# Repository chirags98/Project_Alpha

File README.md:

# Project_Alpha

Changes made:
1) Supply to R8 was changed from -10V to +10V.
2) Track width was increased from 10 mil to 24 mil.
3) Bypass capacitor was added for 8051.
4) GND planewas shifted to bottom layer and given isolation setting of 16 mil.

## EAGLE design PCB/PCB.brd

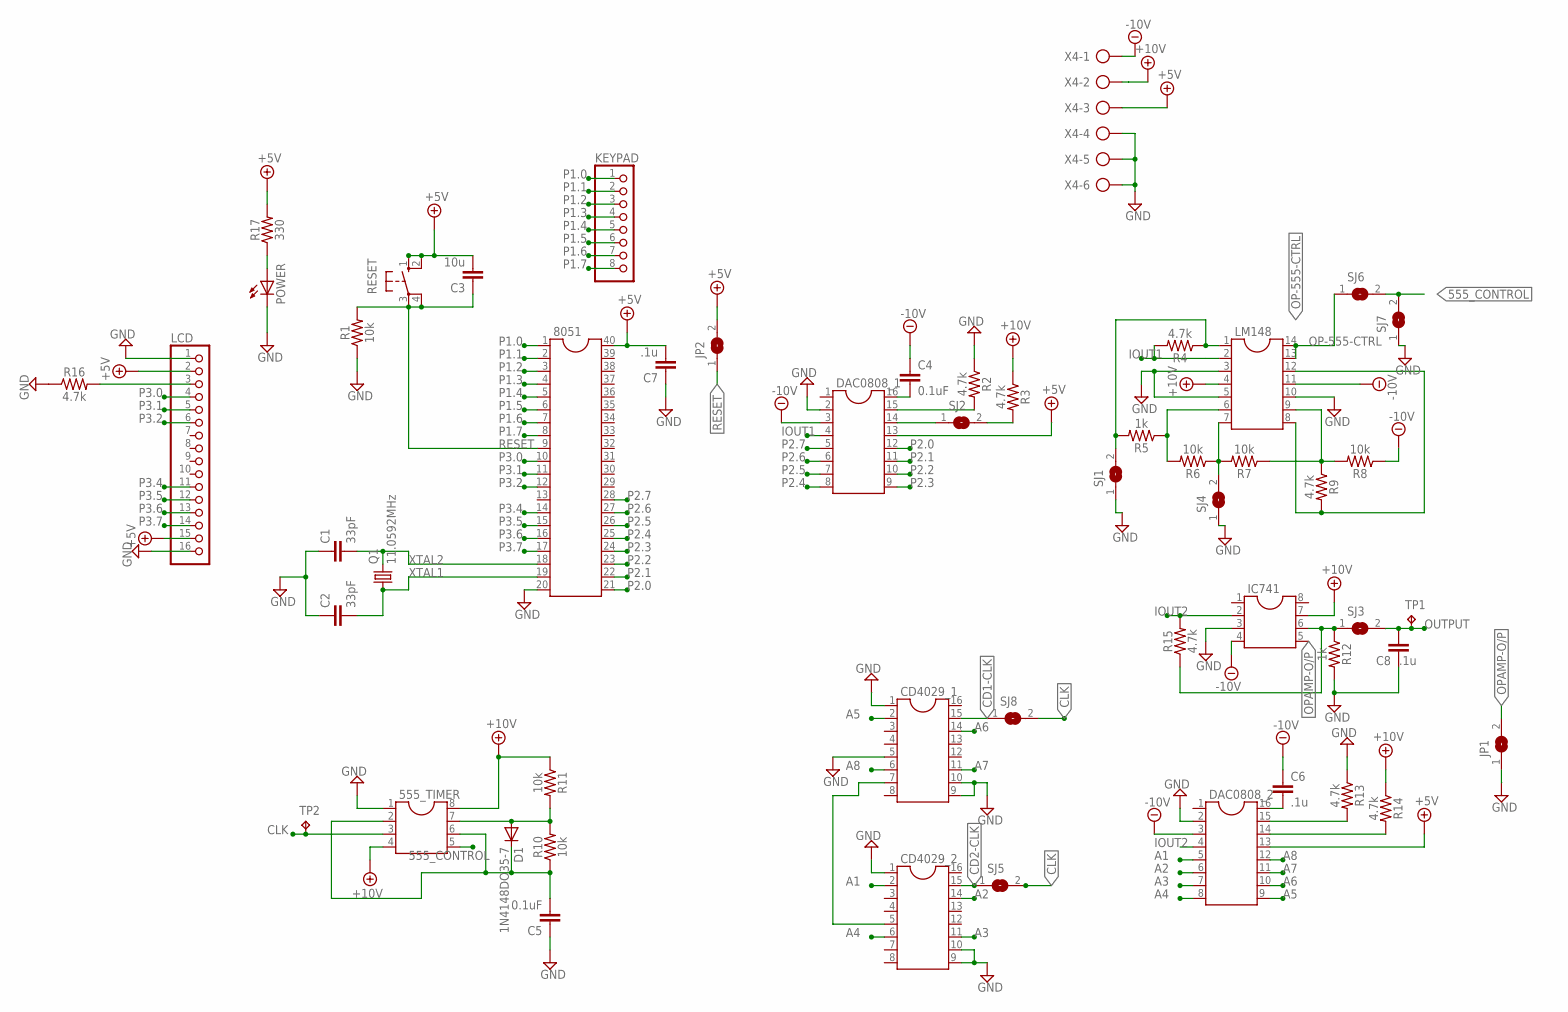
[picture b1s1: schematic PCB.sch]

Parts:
555_TIMER: DIL8; DIL08
8051: DIL40; MPN PIC-USB-4550
C1, C2: 33pF; C025-025X050
C3: 10u; C025-025X050
C4, C5: 0.1uF; C025-025X050
C6, C7, C8: .1u; C025-025X050
CD4029_1, CD4029_2: DIL16
D1: 1N4148DO35-7; DO35-7
DAC0808_1, DAC0808_2: DIL16
IC741: DIL8; DIL08
JP1, JP2: SJ
KEYPAD: PINHD-1X8; 1X08
LCD: PINHD-1X16; 1X16
LM148: DIL14
POWER: LED5MM
Q1: 11.0592MHz; HC49/S; MPN HC49SM-3.6864-30-50-60-16-ATF
R1, R6, R7, R8, R10, R11: 10k; AXIAL-0.3
R2, R3, R4, R9, R13, R14, R15, R16: 4.7k; AXIAL-0.3
R5, R12: 1k; AXIAL-0.3
R17: 330; AXIAL-0.3
RESET: 10-XX; B3F-10XX
SJ1, SJ2, SJ3, SJ4, SJ5, SJ6, SJ7, SJ8: SJ
TP1, TP2: TPPAD1-20; P1-20
X4: AK500/6-H

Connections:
555_CONTROL: 555_TIMER.5, SJ6.2, SJ7.2
+5V: 8051.40, C3.2, C7.2, DAC0808_1.13, DAC0808_2.13, JP2.2, LCD.2, LCD.15, R17.P$2 (2), RESET.1 (S), RESET.2 (S1), X4.3
+10V: 555_TIMER.4, 555_TIMER.8, IC741.7, LM148.4, R3.P$1 (1), R11.P$1 (1), R14.P$1 (1), X4.2
-10V: C4.1, C6.1, DAC0808_1.3, DAC0808_2.3, IC741.4, LM148.11, R8.P$1 (1), X4.1
A1: CD4029_2.2, DAC0808_2.5
A2: CD4029_2.14, DAC0808_2.6
A3: CD4029_2.11, DAC0808_2.7
A4: CD4029_2.6, DAC0808_2.8
A5: CD4029_1.2, DAC0808_2.9
A6: CD4029_1.14, DAC0808_2.10
A7: CD4029_1.11, DAC0808_2.11
A8: CD4029_1.6, DAC0808_2.12
CD1-CLK: CD4029_1.15, SJ8.1
CD2-CLK: CD4029_2.15, SJ5.1
CLK: 555_TIMER.3, SJ5.2, SJ8.2, TP2.TP
GND: 555_TIMER.1, 8051.20, C1.1, C2.1, C5.1, C7.1, C8.1, CD4029_1.1, CD4029_1.5, CD4029_1.9, CD4029_1.10, CD4029_2.1, CD4029_2.9, CD4029_2.10, DAC0808_1.2, DAC0808_2.2, IC741.3, JP1.1, LCD.1, LCD.16, LM148.3, LM148.5, LM148.10, POWER.K (C), R1.P$1 (1), R2.P$1 (1), R12.P$2 (2), R13.P$1 (1), R16.P$1 (1), SJ1.1, SJ4.1, SJ7.1, X4.4, X4.5, X4.6
IOUT1: DAC0808_1.4, LM148.2, R4.P$2 (2)
IOUT2: DAC0808_2.4, IC741.2, R15.P$2 (2)
unnamed: DAC0808_1.15, R2.P$2 (2)
unnamed: R3.P$2 (2), SJ2.2
unnamed: C4.2, DAC0808_1.16
unnamed: LM148.7, R6.P$1 (1), R7.P$2 (2), SJ4.2
unnamed: LM148.1, R4.P$1 (1), R5.P$2 (2), SJ1.2
unnamed: LM148.6, R5.P$1 (1), R6.P$2 (2)
unnamed: LM148.9, R7.P$1 (1), R8.P$2 (2), R9.P$1 (1)
unnamed: 555_TIMER.7, D1.A, R10.P$2 (2), R11.P$2 (2)
unnamed: 555_TIMER.2, 555_TIMER.6, C5.2, D1.C, R10.P$1 (1)
unnamed: DAC0808_2.15, R13.P$2 (2)
unnamed: DAC0808_2.14, R14.P$2 (2)
unnamed: C6.2, DAC0808_2.16
unnamed: CD4029_1.7, CD4029_2.5
unnamed: POWER.A, R17.P$1 (1)
unnamed: DAC0808_1.14, SJ2.1
unnamed: LM148.8, LM148.12, R9.P$2 (2)
unnamed: LCD.3, R16.P$2 (2)
OP-555-CTRL: LM148.13, LM148.14, SJ6.1
OPAMP-O/P: IC741.6, JP1.2, R12.P$1 (1), R15.P$1 (1), SJ3.1
OUTPUT: C8.2, SJ3.2, TP1.TP
P1.0: 8051.1, KEYPAD.1
P1.1: 8051.2, KEYPAD.2
P1.2: 8051.3, KEYPAD.3
P1.3: 8051.4, KEYPAD.4
P1.4: 8051.5, KEYPAD.5
P1.5: 8051.6, KEYPAD.6
P1.6: 8051.7, KEYPAD.7
P1.7: 8051.8, KEYPAD.8
P2.0: 8051.21, DAC0808_1.12
P2.1: 8051.22, DAC0808_1.11
P2.2: 8051.23, DAC0808_1.10
P2.3: 8051.24, DAC0808_1.9
P2.4: 8051.25, DAC0808_1.8
P2.5: 8051.26, DAC0808_1.7
P2.6: 8051.27, DAC0808_1.6
P2.7: 8051.28, DAC0808_1.5
P3.0: 8051.10, LCD.4
P3.1: 8051.11, LCD.5
P3.2: 8051.12, LCD.6
P3.4: 8051.14, LCD.11
P3.5: 8051.15, LCD.12
P3.6: 8051.16, LCD.13
P3.7: 8051.17, LCD.14
RESET: 8051.9, C3.1, JP2.1, R1.P$2 (2), RESET.3, RESET.4 (P1)
XTAL1: 8051.19, C2.2, Q1.1
XTAL2: 8051.18, C1.2, Q1.2

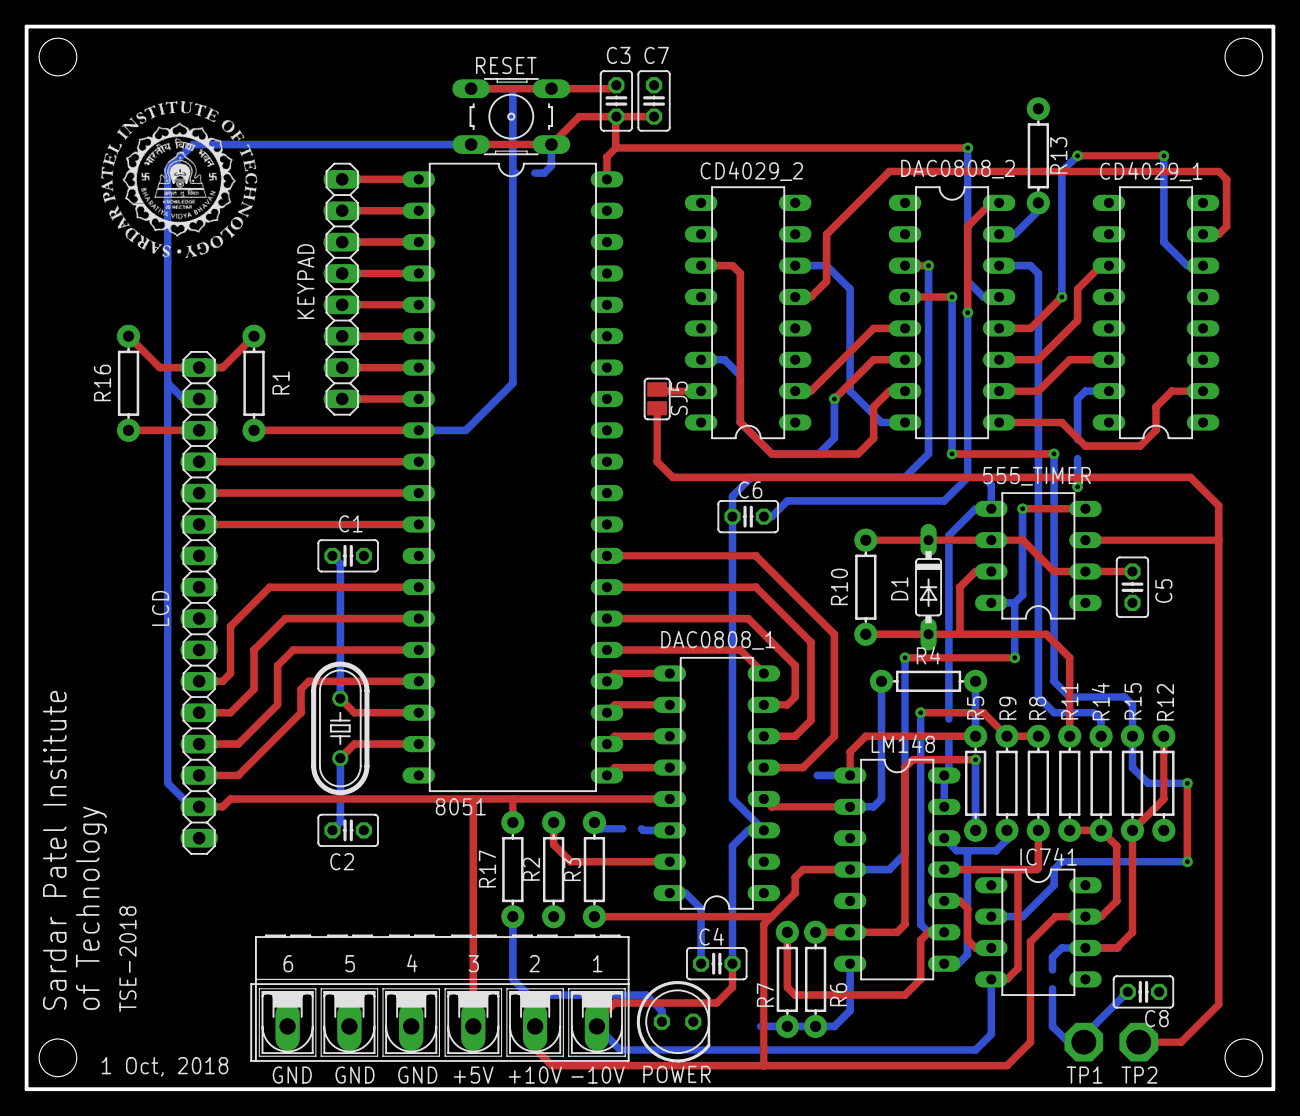
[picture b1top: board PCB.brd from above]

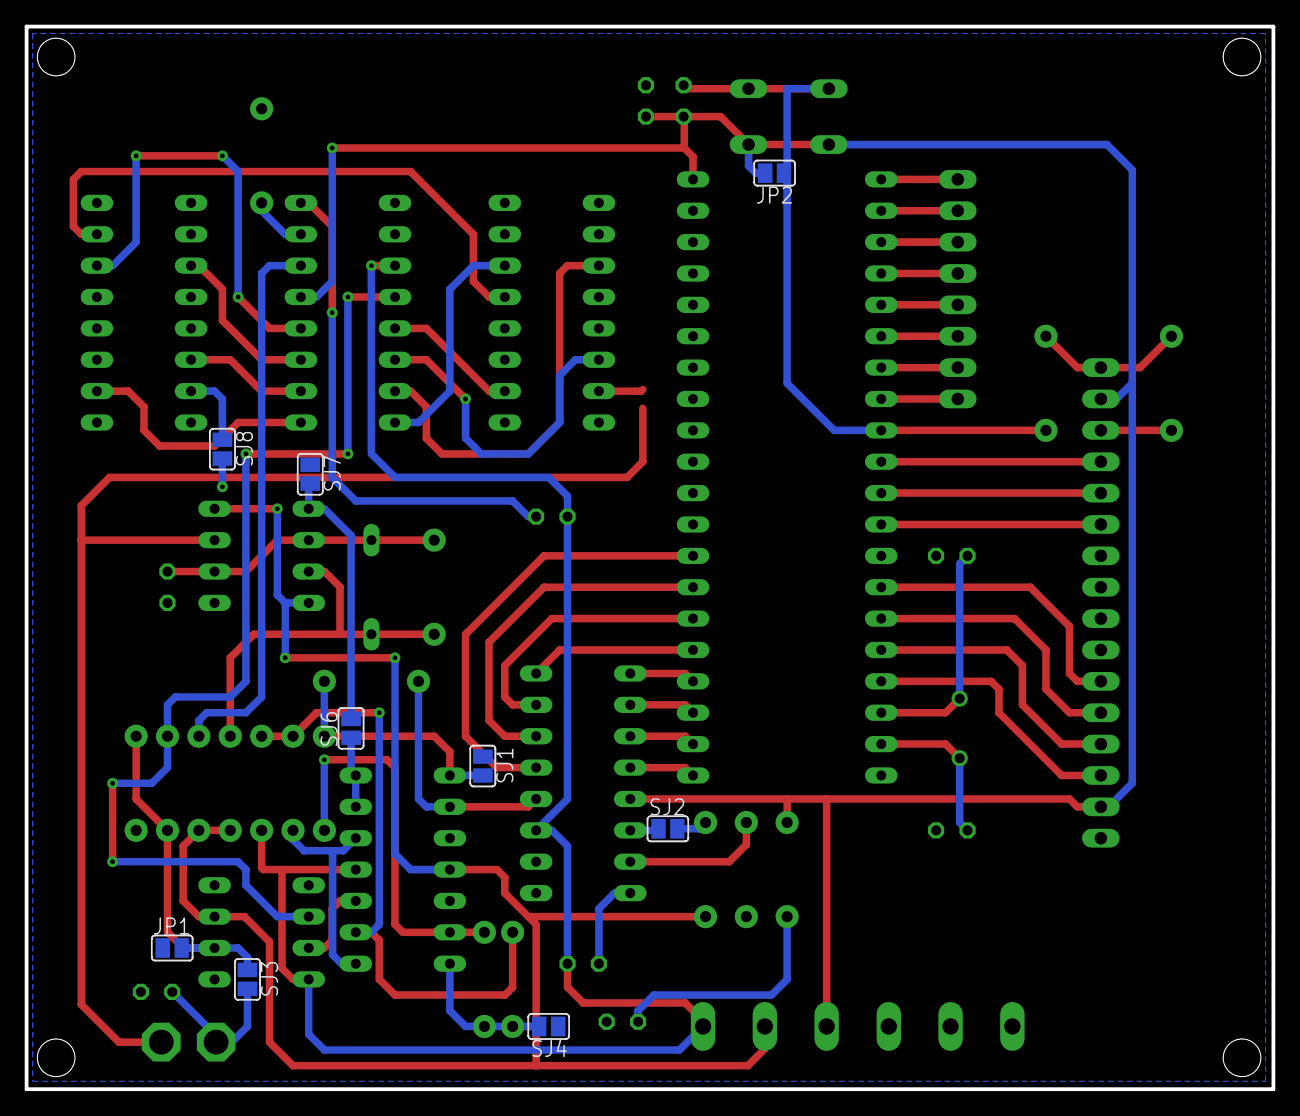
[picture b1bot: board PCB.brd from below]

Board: 2 copper layers, 100.9 x 86.0 mm, 52 parts (9 on the bottom side), 64 nets.

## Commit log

2018-09-15 Added board after initial routing
2018-09-16 Add files via upload
    Changes made:
    1) Changed supply to R8 (from -10V to +10V).
    2) Increased all track widths from 10 mil to 24 mil.
    3) Added a bypass capacitor for 8051.
    4) Shifted GND plane to bottom layer and gave isolation setting of 16 mil.
2018-09-20 Add files via upload
    Proteus Simulation
2018-09-30 PCB Verified
    Changes done:
    1) Supply and resistor value change in Adder Subtractor circuit.
    2)No more potential divider from 555 output.
    3)Correction in Counter 2 circuit(Pins 14 and 11 were given to wrong outputs)
    4)Final output resistor included(R12)
    5)All final values added to schematic.
2018-09-30 Added adithya's files after verification
2018-09-30 Silkscreen, mounting holes, power/ip screw terminals
2018-10-01 Final-for manufacturing
2018-10-10 Commit since not sure if any changes are made
2018-10-18 During assembly - changed some values

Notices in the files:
parts and their libraries:
SparkFun-Resistors: Licensing: Creative Commons ShareAlike 4.0 International - https://creativecommons.org/licenses/by-sa/4.0
